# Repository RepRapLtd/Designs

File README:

This is just a dump of all my various designs for things that are not
specifically RepRap.

Some of the things here are OS designs that are not mine, and have just been placed
in this directory by me for convenience.

AB
24/2/2015

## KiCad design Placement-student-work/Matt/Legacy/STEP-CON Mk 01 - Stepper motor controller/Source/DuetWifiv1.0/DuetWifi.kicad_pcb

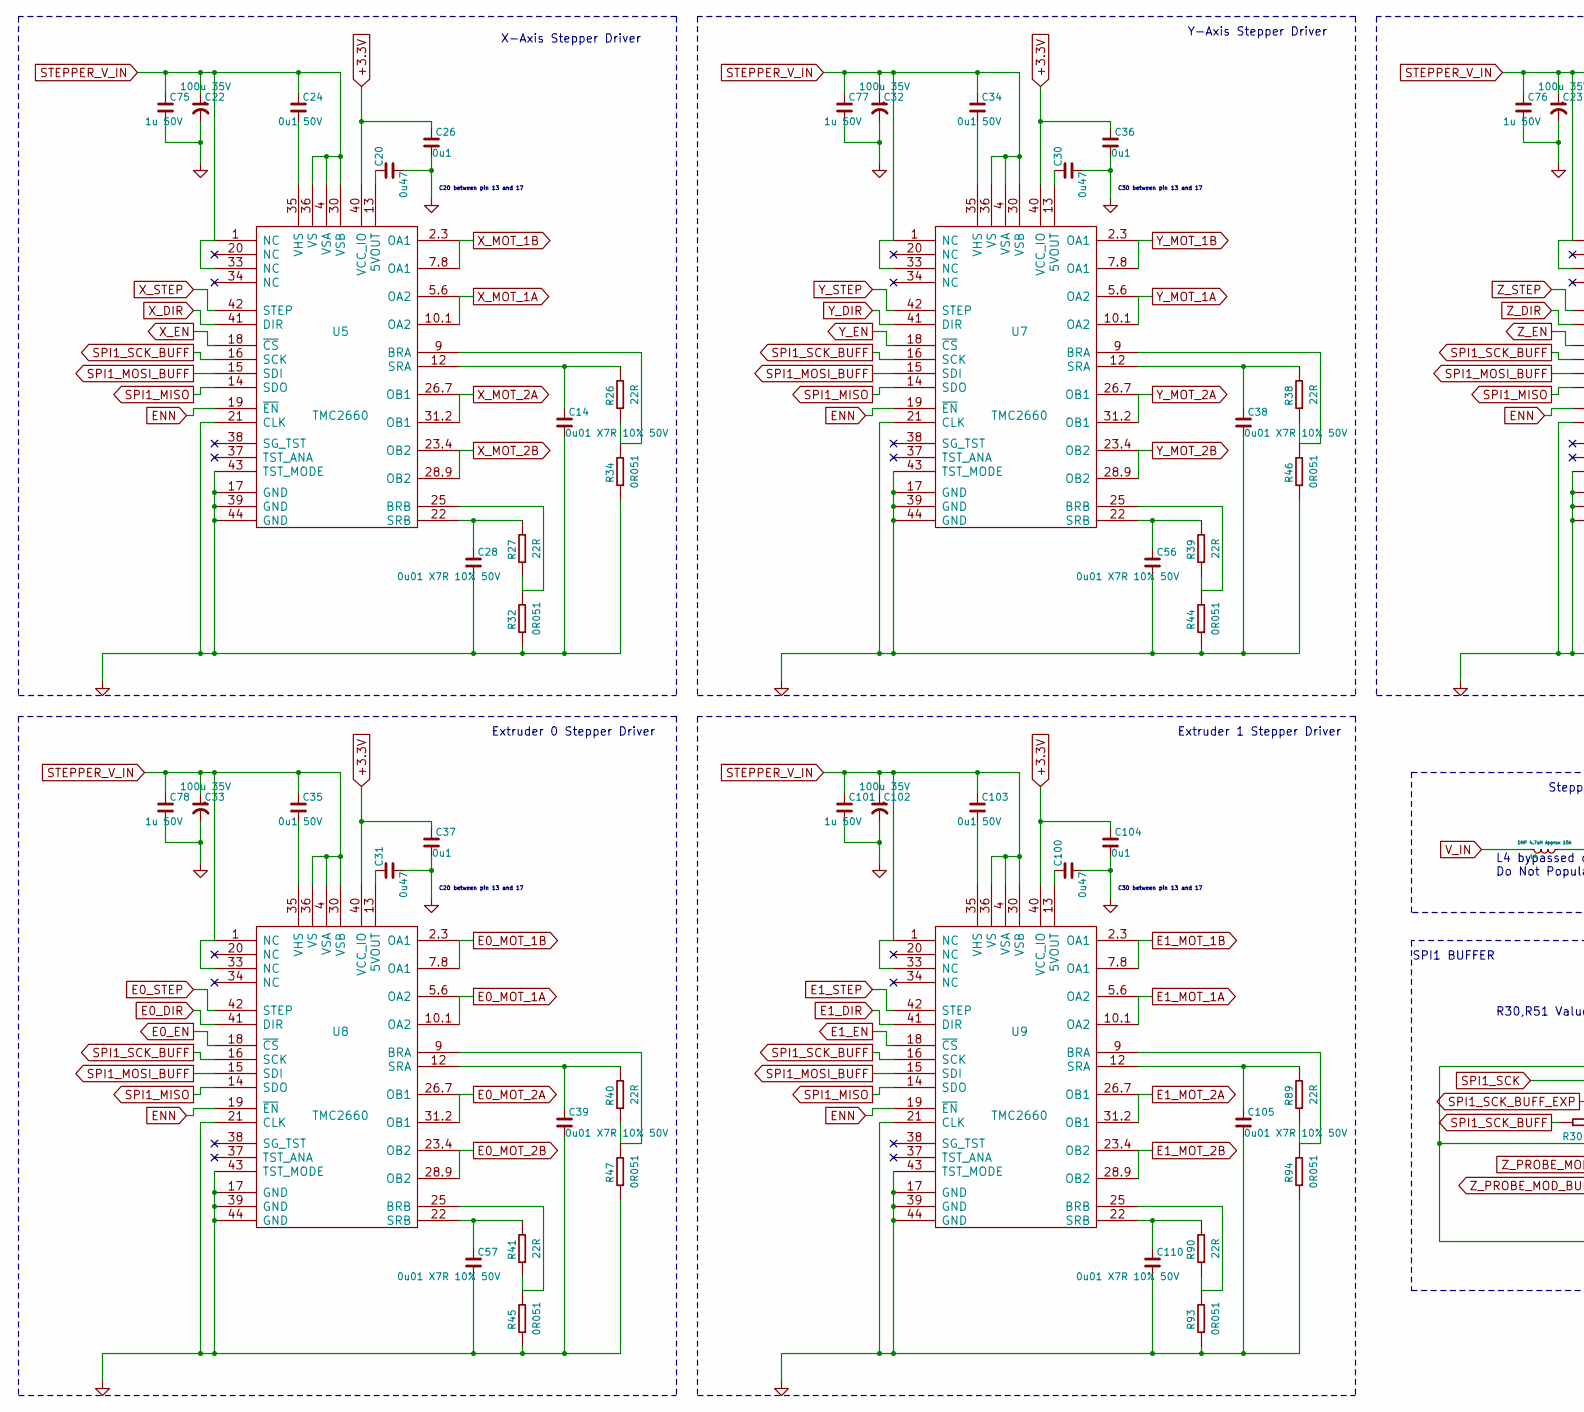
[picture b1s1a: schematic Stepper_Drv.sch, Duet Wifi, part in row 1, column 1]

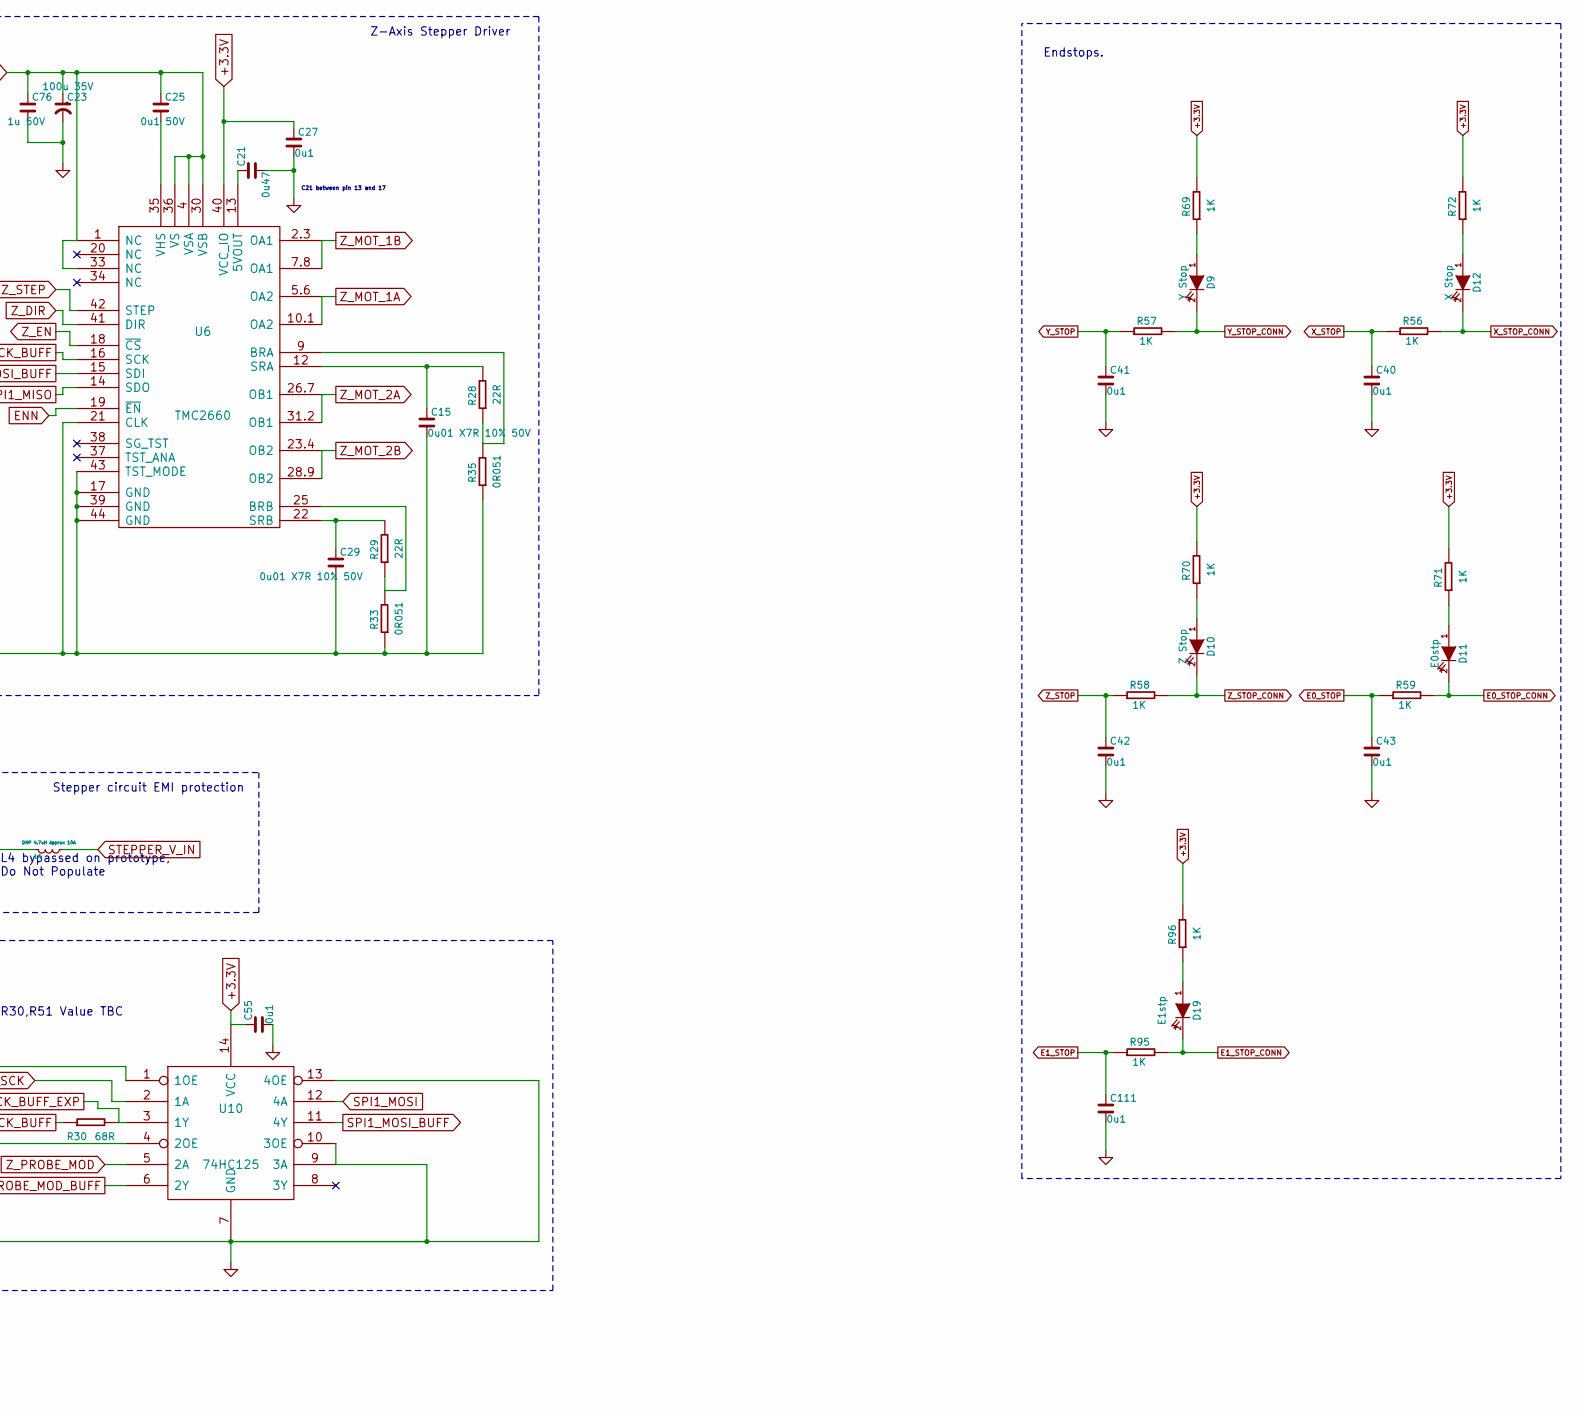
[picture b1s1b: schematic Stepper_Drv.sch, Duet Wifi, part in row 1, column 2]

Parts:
C14, C15, C28, C29, C38, C39, C56, C57, C105, C110: 0u01 X7R 10% 50V; C_0603
C20, C21, C30, C31, C100: 0u47; C_0603
C22, C23, C32, C33, C102: 100u 35V; C_ELEC_6.3x7.7
C24, C25, C34, C35, C103: 0u1 50V; C_0603
C26, C27, C36, C37, C40, C41, C42, C43, C55, C104, C111: 0u1; C_0603
C75, C76, C77, C78, C101: 1u 50V; C_0603
D9: Y Stop; D_0603
D10: Z Stop; D_0603
D11: E0stp; D_0603
D12: X Stop; D_0603
D19: E1stp; D_0603
L4: DNP 4.7uH Approx 10A; TPC-XL-Bridged
R26, R27, R28, R29, R38, R39, R40, R41, R89, R90: 22R; R_0603
R30: 68R; R_0603
R32, R33, R34, R35, R44, R45, R46, R47, R93, R94: 0R051; R_1206
R56, R57, R58, R59, R69, R70, R71, R72, R95, R96: 1K; R_0603
U5, U6, U7, U8, U9: TMC2660
U10: 74HC125; TSSOP-14

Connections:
+3.3V: C26.1, C27.1, C36.1, C37.1, C55.1, C104.1, R69.2, R70.2, R71.2, R72.2, R96.2, U5.40 (VCC_IO), U6.40 (VCC_IO), U7.40 (VCC_IO), U8.40 (VCC_IO), U9.40 (VCC_IO), U10.14 (VCC); also elsewhere on the board
E0_DIR: U8.41 (DIR); also elsewhere on the board
E0_EN: U8.18 (~CS); also elsewhere on the board
E0_MOT_1A: U8.5.6 (OA2), U8.10.1 (OA2); also elsewhere on the board
E0_MOT_1B: U8.2.3 (OA1), U8.7.8 (OA1); also elsewhere on the board
E0_MOT_2A: U8.26.7 (OB1), U8.31.2 (OB1); also elsewhere on the board
E0_MOT_2B: U8.23.4 (OB2), U8.28.9 (OB2); also elsewhere on the board
E0_STEP: U8.42 (STEP); also elsewhere on the board
E0_STOP: C43.1, R59.1; also elsewhere on the board
E0_STOP_CONN: D11.2 (K), R59.2; also elsewhere on the board
E1_DIR: U9.41 (DIR); also elsewhere on the board
E1_EN: U9.18 (~CS); also elsewhere on the board
E1_MOT_1A: U9.5.6 (OA2), U9.10.1 (OA2); also elsewhere on the board
E1_MOT_1B: U9.2.3 (OA1), U9.7.8 (OA1); also elsewhere on the board
E1_MOT_2A: U9.26.7 (OB1), U9.31.2 (OB1); also elsewhere on the board
E1_MOT_2B: U9.23.4 (OB2), U9.28.9 (OB2); also elsewhere on the board
E1_STEP: U9.42 (STEP); also elsewhere on the board
E1_STOP: C111.1, R95.1; also elsewhere on the board
E1_STOP_CONN: D19.2 (K), R95.2; also elsewhere on the board
ENN: U5.19 (~EN), U6.19 (~EN), U7.19 (~EN), U8.19 (~EN), U9.19 (~EN); also elsewhere on the board
GND: C14.2, C15.2, C20.2, C21.2, C22.2, C23.2, C26.2, C27.2, C28.2, C29.2, C30.2, C31.2, C32.2, C33.2, C36.2, C37.2, C38.2, C39.2, C40.2, C41.2, C42.2, C43.2, C55.2, C56.2, C57.2, C75.2, C76.2, C77.2, C78.2, C100.2, C101.2, C102.2, C104.2, C105.2, C110.2, C111.2, R32.1, R33.1, R34.1, R35.1, R44.1, R45.1, R46.1, R47.1, R93.1, R94.1, U5.17 (GND), U5.21 (CLK), U5.39 (GND), U5.43 (TST_MODE), U5.44 (GND), U6.17 (GND), U6.21 (CLK), U6.39 (GND), U6.43 (TST_MODE), U6.44 (GND), U7.17 (GND), U7.21 (CLK), U7.39 (GND), U7.43 (TST_MODE), U7.44 (GND), U8.17 (GND), U8.21 (CLK), U8.39 (GND), U8.43 (TST_MODE), U8.44 (GND), U9.17 (GND), U9.21 (CLK), U9.39 (GND), U9.43 (TST_MODE), U9.44 (GND), U10.1 (1OE), U10.4 (2OE), U10.7 (GND), U10.9 (3A), U10.10 (3OE), U10.13 (4OE); also elsewhere on the board
unnamed: C14.1, R26.2, U5.12 (SRA)
unnamed: C15.1, R28.2, U6.12 (SRA)
unnamed: C20.1, U5.13 (5VOUT)
unnamed: C21.1, U6.13 (5VOUT)
unnamed: C24.2, U5.35 (VHS)
unnamed: C25.2, U6.35 (VHS)
unnamed: C28.1, R27.2, U5.22 (SRB)
unnamed: C29.1, R29.2, U6.22 (SRB)
unnamed: C30.1, U7.13 (5VOUT)
unnamed: C31.1, U8.13 (5VOUT)
unnamed: C34.2, U7.35 (VHS)
unnamed: C35.2, U8.35 (VHS)
unnamed: C38.1, R38.2, U7.12 (SRA)
unnamed: C39.1, R40.2, U8.12 (SRA)
unnamed: C56.1, R39.2, U7.22 (SRB)
unnamed: C57.1, R41.2, U8.22 (SRB)
unnamed: C100.1, U9.13 (5VOUT)
unnamed: C103.2, U9.35 (VHS)
unnamed: C105.1, R89.2, U9.12 (SRA)
unnamed: C110.1, R90.2, U9.22 (SRB)
unnamed: D9.1 (A), R69.1
unnamed: D10.1 (A), R70.1
unnamed: D11.1 (A), R71.1
unnamed: D12.1 (A), R72.1
unnamed: D19.1 (A), R96.1
unnamed: R26.1, R34.2, U5.9 (BRA)
unnamed: R27.1, R32.2, U5.25 (BRB)
unnamed: R28.1, R35.2, U6.9 (BRA)
unnamed: R29.1, R33.2, U6.25 (BRB)
unnamed: R38.1, R46.2, U7.9 (BRA)
unnamed: R39.1, R44.2, U7.25 (BRB)
unnamed: R40.1, R47.2, U8.9 (BRA)
unnamed: R41.1, R45.2, U8.25 (BRB)
unnamed: R89.1, R94.2, U9.9 (BRA)
unnamed: R90.1, R93.2, U9.25 (BRB)
SPI1_MISO: U5.14 (SDO), U6.14 (SDO), U7.14 (SDO), U8.14 (SDO), U9.14 (SDO); also elsewhere on the board
SPI1_MOSI: U10.12 (4A); also elsewhere on the board
SPI1_MOSI_BUFF: U5.15 (SDI), U6.15 (SDI), U7.15 (SDI), U8.15 (SDI), U9.15 (SDI), U10.11 (4Y); also elsewhere on the board
SPI1_SCK: U10.2 (1A); also elsewhere on the board
SPI1_SCK_BUFF: R30.1, U5.16 (SCK), U6.16 (SCK), U7.16 (SCK), U8.16 (SCK), U9.16 (SCK); also elsewhere on the board
SPI1_SCK_BUFF_EXP: R30.2, U10.3 (1Y); also elsewhere on the board
STEPPER_V_IN: C22.1, C23.1, C24.1, C25.1, C32.1, C33.1, C34.1, C35.1, C75.1, C76.1, C77.1, C78.1, C101.1, C102.1, C103.1, L4.2 (B), U5.1 (NC), U5.4 (VSA), U5.30 (VSB), U5.33 (NC), U5.36 (VS), U6.1 (NC), U6.4 (VSA), U6.30 (VSB), U6.33 (NC), U6.36 (VS), U7.1 (NC), U7.4 (VSA), U7.30 (VSB), U7.33 (NC), U7.36 (VS), U8.1 (NC), U8.4 (VSA), U8.30 (VSB), U8.33 (NC), U8.36 (VS), U9.1 (NC), U9.4 (VSA), U9.30 (VSB), U9.33 (NC), U9.36 (VS)
V_IN: L4.1 (A); also elsewhere on the board
X_DIR: U5.41 (DIR); also elsewhere on the board
X_EN: U5.18 (~CS); also elsewhere on the board
X_MOT_1A: U5.5.6 (OA2), U5.10.1 (OA2); also elsewhere on the board
X_MOT_1B: U5.2.3 (OA1), U5.7.8 (OA1); also elsewhere on the board
X_MOT_2A: U5.26.7 (OB1), U5.31.2 (OB1); also elsewhere on the board
X_MOT_2B: U5.23.4 (OB2), U5.28.9 (OB2); also elsewhere on the board
X_STEP: U5.42 (STEP); also elsewhere on the board
X_STOP: C40.1, R56.1; also elsewhere on the board
X_STOP_CONN: D12.2 (K), R56.2; also elsewhere on the board
Y_DIR: U7.41 (DIR); also elsewhere on the board
Y_EN: U7.18 (~CS); also elsewhere on the board
Y_MOT_1A: U7.5.6 (OA2), U7.10.1 (OA2); also elsewhere on the board
Y_MOT_1B: U7.2.3 (OA1), U7.7.8 (OA1); also elsewhere on the board
Y_MOT_2A: U7.26.7 (OB1), U7.31.2 (OB1); also elsewhere on the board
Y_MOT_2B: U7.23.4 (OB2), U7.28.9 (OB2); also elsewhere on the board
Y_STEP: U7.42 (STEP); also elsewhere on the board
Y_STOP: C41.1, R57.1; also elsewhere on the board
Y_STOP_CONN: D9.2 (K), R57.2; also elsewhere on the board
Z_DIR: U6.41 (DIR); also elsewhere on the board
Z_EN: U6.18 (~CS); also elsewhere on the board
Z_MOT_1A: U6.5.6 (OA2), U6.10.1 (OA2); also elsewhere on the board
Z_MOT_1B: U6.2.3 (OA1), U6.7.8 (OA1); also elsewhere on the board
Z_MOT_2A: U6.26.7 (OB1), U6.31.2 (OB1); also elsewhere on the board
Z_MOT_2B: U6.23.4 (OB2), U6.28.9 (OB2); also elsewhere on the board
Z_PROBE_MOD: U10.5 (2A); also elsewhere on the board
Z_PROBE_MOD_BUFF: U10.6 (2Y); also elsewhere on the board
Z_STEP: U6.42 (STEP); also elsewhere on the board
Z_STOP: C42.1, R58.1; also elsewhere on the board
Z_STOP_CONN: D10.2 (K), R58.2; also elsewhere on the board

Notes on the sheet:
Endstops.
Extruder 0 Stepper Driver
Y-Axis Stepper Driver
X-Axis Stepper Driver
Extruder 1 Stepper Driver
Stepper circuit EMI protection
L4 bypassed on prototype, Do Not Populate
SPI1 BUFFER
C20 between pin 13 and 17
C30 between pin 13 and 17
Z-Axis Stepper Driver
C21 between pin 13 and 17
R30,R51 Value TBC

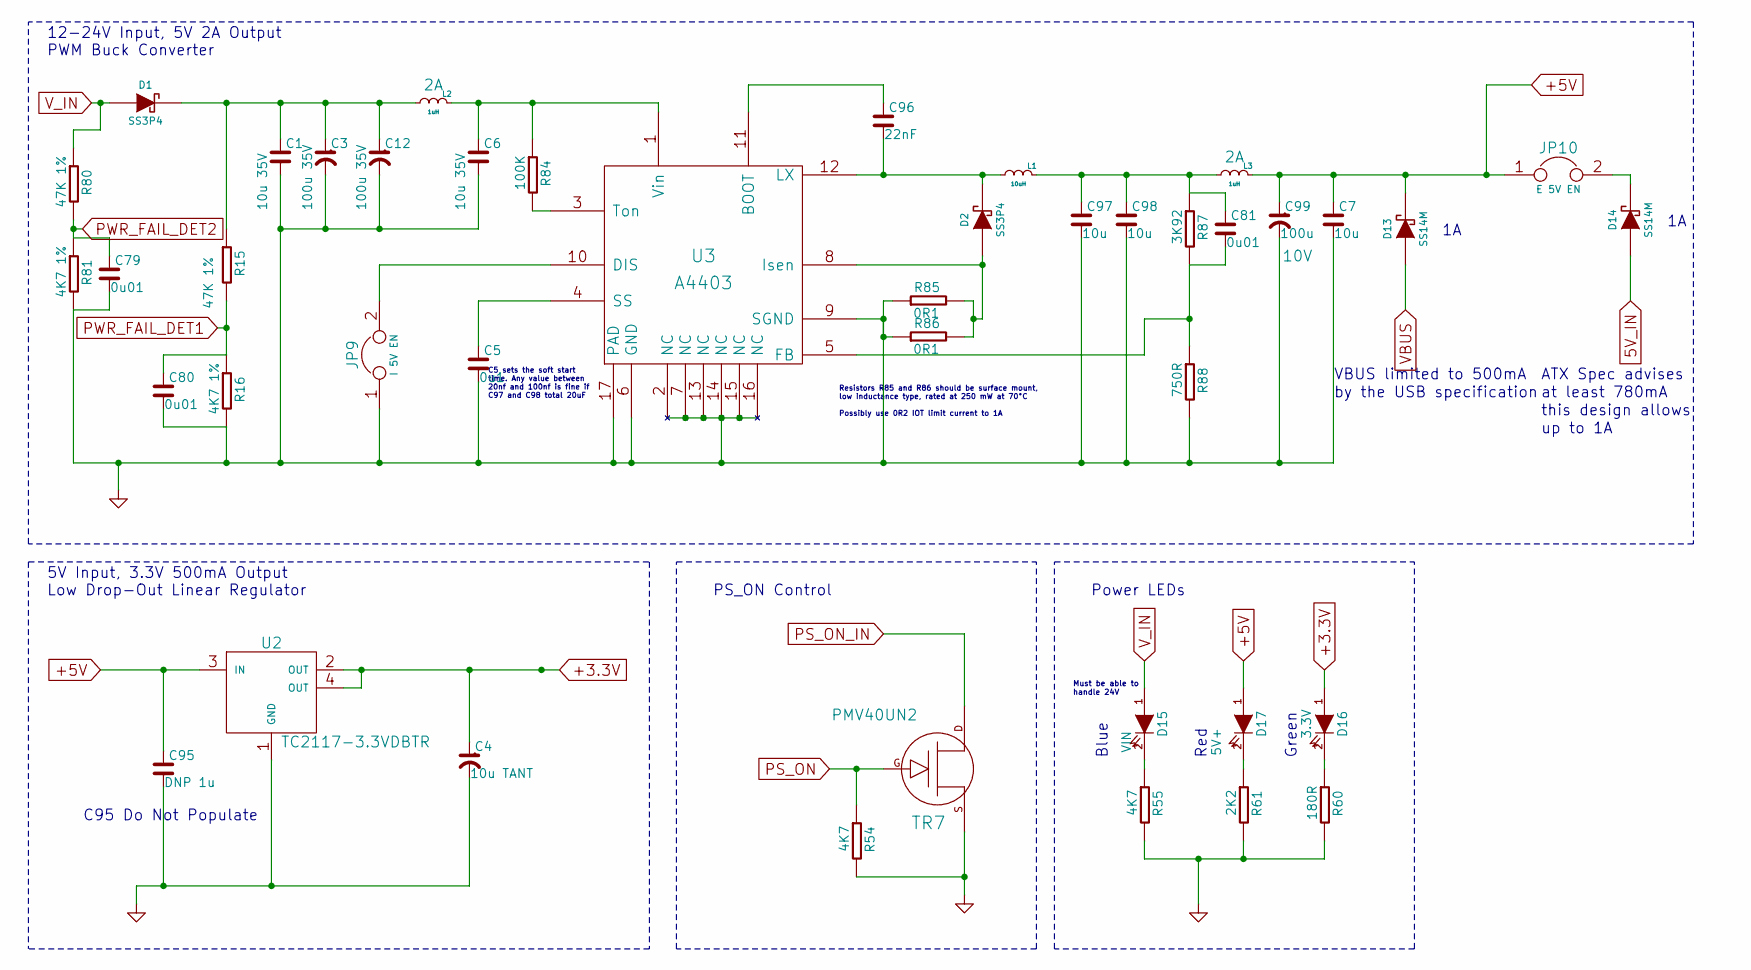
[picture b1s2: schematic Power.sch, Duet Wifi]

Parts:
C1, C6: 10u 35V; C_1206
C3, C12: 100u 35V; C_ELEC_6.3x7.7
C4: 10u TANT; C_1206_pol
C5: 0u1; C_0603
C7, C97, C98: 10u; C_0805
C79, C80, C81: 0u01; C_0603
C95: DNP 1u; C_0603
C96: 22nF; C_0603
C99: 100u; C_ELEC_6.3x7.7; Voltage 10V
D1, D2: SS3P4; DO-220AA
D13, D14: SS14M; uSMA
D15: VIN; D_0603
D16: 3.3V; D_0603
D17: 5V+; D_0603
JP9: I 5V EN; JUMPER
JP10: E 5V EN; JUMPER
L1: 10uH; L_6x6
L2, L3: 1uH; C_1210; Rating 2A
R15, R80: 47K 1%; R_0603
R16, R81: 4K7 1%; R_0603
R54, R55: 4K7; R_0603
R60: 180R; R_0603
R61: 2K2; R_0603
R84: 100K; R_0603
R85, R86: 0R1; R_1206
R87: 3K92; R_0603
R88: 750R; R_0603
TR7: PMV40UN2; SOT-23
U2: TC2117-3.3VDBTR; SOT-223
U3: A4403; QFN16-4x4

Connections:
5V_IN: D14.1 (A); also elsewhere on the board
+3.3V: C4.1, D16.1 (A), U2.2 (OUT), U2.4 (OUT); also elsewhere on the board
+5V: C7.1, C95.1, C99.1, D13.2 (K), D17.1 (A), JP10.1, L3.1 (A), U2.3 (IN); also elsewhere on the board
GND: C1.2, C3.2, C4.2, C5.2, C6.2, C7.2, C12.2, C79.2, C80.2, C95.2, C97.2, C98.2, C99.2, JP9.1, R16.2, R54.2, R55.2, R60.2, R61.2, R81.2, R85.1, R86.1, R88.2, TR7.S, U2.1 (GND), U3.2 (NC), U3.6 (GND), U3.7 (NC), U3.9 (SGND), U3.13 (NC), U3.14 (NC), U3.15 (NC), U3.16 (NC), U3.17 (PAD); also elsewhere on the board
unnamed: C1.1, C3.1, C12.1, D1.2 (K), L2.2 (B), R15.1
unnamed: C5.1, U3.4 (SS)
unnamed: C6.1, L2.1 (A), R84.1, U3.1 (Vin)
unnamed: C81.1, C97.1, C98.1, L1.1 (A), L3.2 (B), R87.1
unnamed: C81.2, R87.2, R88.1, U3.5 (FB)
unnamed: C96.1, U3.11 (BOOT)
unnamed: C96.2, D2.2 (K), L1.2 (B), U3.12 (LX)
unnamed: D2.1 (A), R85.2, R86.2, U3.8 (Isen)
unnamed: D14.2 (K), JP10.2
unnamed: D15.2 (K), R55.1
unnamed: D16.2 (K), R60.1
unnamed: D17.2 (K), R61.1
unnamed: JP9.2, U3.10 (DIS)
unnamed: R84.2, U3.3 (Ton)
PS_ON: R54.1, TR7.G; also elsewhere on the board
PS_ON_IN: TR7.D; also elsewhere on the board
PWR_FAIL_DET1: C80.1, R15.2, R16.1; also elsewhere on the board
PWR_FAIL_DET2: C79.1, R80.2, R81.1; also elsewhere on the board
VBUS: D13.1 (A); also elsewhere on the board
V_IN: D1.1 (A), D15.1 (A), R80.1; also elsewhere on the board

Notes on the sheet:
PS_ON Control
up to 1A
this design allows
at least 780mA
ATX Spec advises
by the USB specification
VBUS limited to 500mA
5V Input, 3.3V 500mA Output Low Drop-Out Linear Regulator
12-24V Input, 5V 2A Output PWM Buck Converter
Resistors R85 and R86 should be surface mount, low inductance type, rated at 250 mW at 70°C Possibly use 0R2 IOT limit current to 1A
C5 sets the soft start time. Any value between 20nf and 100nf is fine if C97 and C98 total 20uF
Power LEDs
Must be able to handle 24V
Blue
Red
Green
C95 Do Not Populate

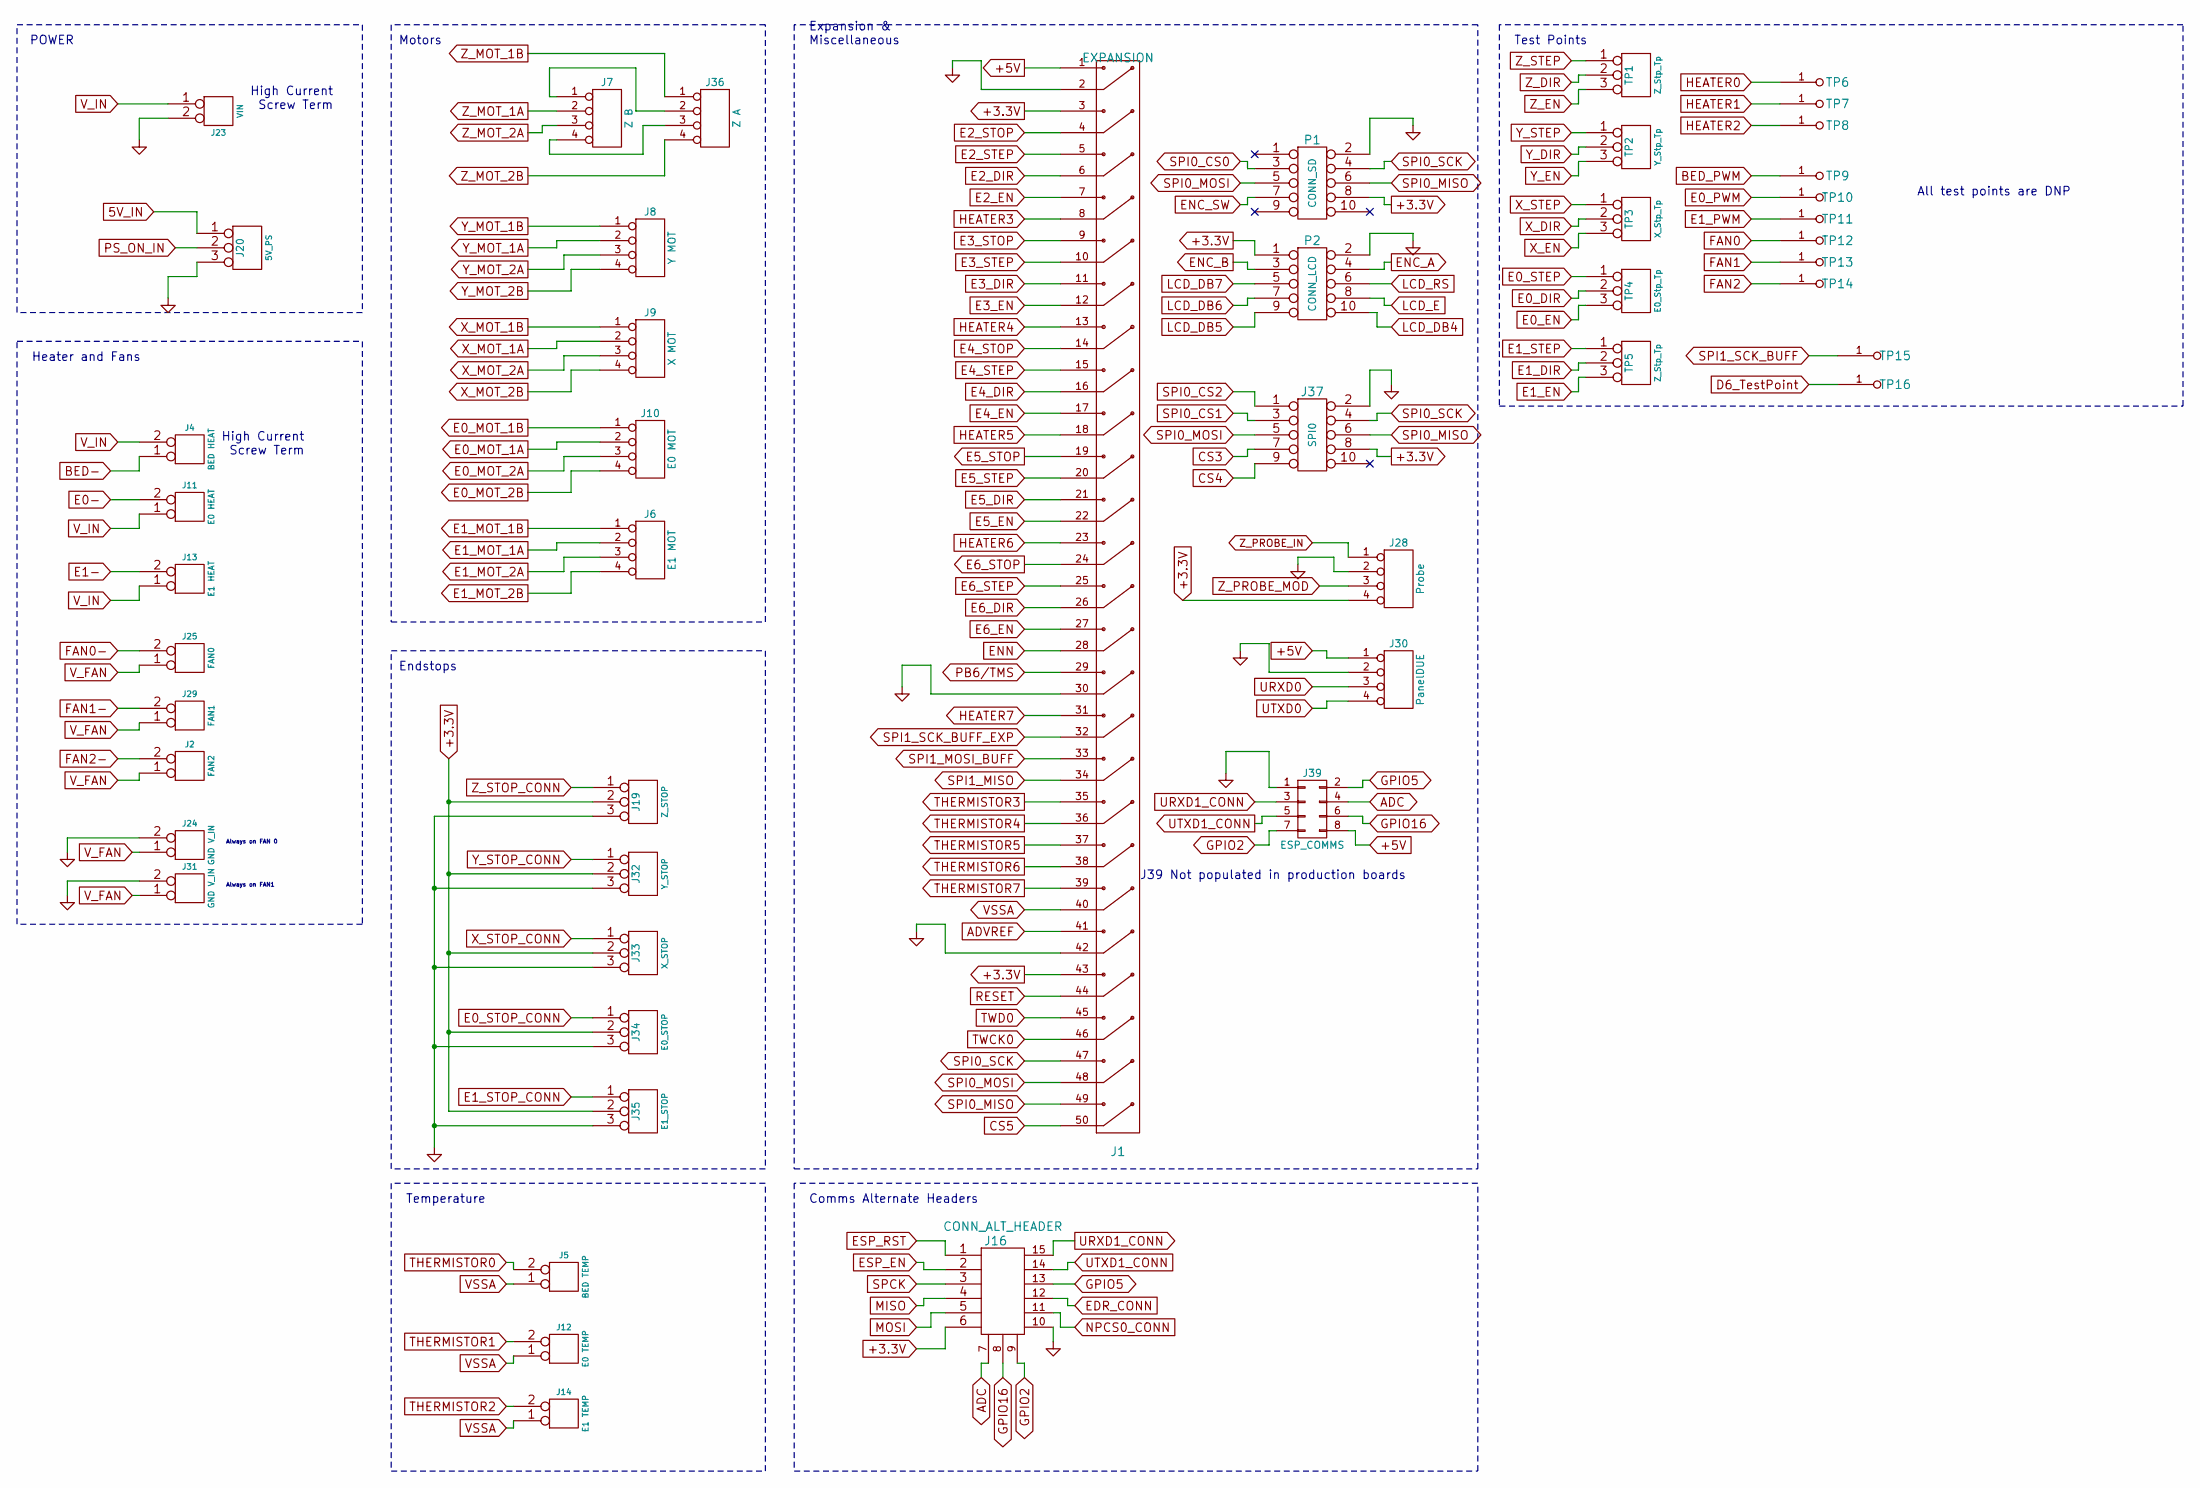
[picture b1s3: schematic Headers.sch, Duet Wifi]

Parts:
J1: EXPANSION; PIN_ARRAY_25X2
J2: FAN2; PIN_ARRAY_2X1
J4: BED HEAT; TERM_2-WAY_6.35mm
J5: BED TEMP; PIN_ARRAY_2X1
J6: E1 MOT; PIN_ARRAY_4x1
J7: Z B; PIN_ARRAY_4x1
J8: Y MOT; PIN_ARRAY_4x1
J9: X MOT; PIN_ARRAY_4x1
J10: E0 MOT; PIN_ARRAY_4x1
J11: E0 HEAT; 3.5MM_2X1
J12: E0 TEMP; PIN_ARRAY_2X1
J13: E1 HEAT; 3.5MM_2X1
J14: E1 TEMP; PIN_ARRAY_2X1
J16: CONN_ALT_HEADER
J19: Z_STOP; PIN_ARRAY_3X1
J20: 5V_PS; PIN_ARRAY_3X1
J23: VIN; TERM_2-WAY_6.35mm
J24, J31: GND V_IN; PIN_ARRAY_2X1
J25: FAN0; PIN_ARRAY_2X1
J28: Probe; PIN_ARRAY_4x1
J29: FAN1; PIN_ARRAY_2X1
J30: PanelDUE; PIN_ARRAY_4x1
J32: Y_STOP; PIN_ARRAY_3X1
J33: X_STOP; PIN_ARRAY_3X1
J34: E0_STOP; PIN_ARRAY_3X1
J35: E1_STOP; PIN_ARRAY_3X1
J36: Z A; PIN_ARRAY_4x1
J37: SPI0; MAX_TEMP_DB
J39: ESP_COMMS; CONN_4x2
P1: CONN_SD; IDC_PIN_ARRAY_5x2
P2: CONN_LCD; IDC_PIN_ARRAY_5x2
TP1, TP5: Z_Stp_Tp; CONN_3x1
TP2: Y_Stp_Tp; CONN_3x1
TP3: X_Stp_Tp; CONN_3x1
TP4: E0_Stp_Tp; CONN_3x1
TP6, TP7, TP8, TP9, TP10, TP11, TP12, TP13, TP14, TP15, TP16: TP; TP_via

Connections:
5V_IN: J20.1; also elsewhere on the board
+3.3V: J1.3, J1.43, J16.6, J19.2 (PM), J28.4, J32.2 (PM), J33.2 (PM), J34.2 (PM), J35.2 (PM), J37.8, P1.8, P2.1; also elsewhere on the board
+5V: J1.1, J30.1, J39.8; also elsewhere on the board
ADC: J16.7, J39.4; also elsewhere on the board
ADVREF: J1.41; also elsewhere on the board
BED-: J4.1; also elsewhere on the board
BED_PWM: TP9.1; also elsewhere on the board
CS3: J37.7; also elsewhere on the board
CS4: J37.9; also elsewhere on the board
CS5: J1.50; also elsewhere on the board
D6_TestPoint: TP16.1; also elsewhere on the board
E0-: J11.2 (PM); also elsewhere on the board
E0_DIR: TP4.2 (PM); also elsewhere on the board
E0_EN: TP4.3; also elsewhere on the board
E0_MOT_1A: J10.2; also elsewhere on the board
E0_MOT_1B: J10.1; also elsewhere on the board
E0_MOT_2A: J10.3; also elsewhere on the board
E0_MOT_2B: J10.4; also elsewhere on the board
E0_PWM: TP10.1; also elsewhere on the board
E0_STEP: TP4.1; also elsewhere on the board
E0_STOP_CONN: J34.1; also elsewhere on the board
E1-: J13.2 (PM); also elsewhere on the board
E1_DIR: TP5.2 (PM); also elsewhere on the board
E1_EN: TP5.3; also elsewhere on the board
E1_MOT_1A: J6.2; also elsewhere on the board
E1_MOT_1B: J6.1; also elsewhere on the board
E1_MOT_2A: J6.3; also elsewhere on the board
E1_MOT_2B: J6.4; also elsewhere on the board
E1_PWM: TP11.1; also elsewhere on the board
E1_STEP: TP5.1; also elsewhere on the board
E1_STOP_CONN: J35.1; also elsewhere on the board
E2_DIR: J1.6; also elsewhere on the board
E2_EN: J1.7; also elsewhere on the board
E2_STEP: J1.5; also elsewhere on the board
E2_STOP: J1.4; also elsewhere on the board
E3_DIR: J1.11; also elsewhere on the board
E3_EN: J1.12; also elsewhere on the board
E3_STEP: J1.10; also elsewhere on the board
E3_STOP: J1.9; also elsewhere on the board
E4_DIR: J1.16; also elsewhere on the board
E4_EN: J1.17; also elsewhere on the board
E4_STEP: J1.15; also elsewhere on the board
E4_STOP: J1.14; also elsewhere on the board
E5_DIR: J1.21; also elsewhere on the board
E5_EN: J1.22; also elsewhere on the board
E5_STEP: J1.20; also elsewhere on the board
E5_STOP: J1.19; also elsewhere on the board
E6_DIR: J1.26; also elsewhere on the board
E6_EN: J1.27; also elsewhere on the board
E6_STEP: J1.25; also elsewhere on the board
E6_STOP: J1.24; also elsewhere on the board
EDR_CONN: J16.12; also elsewhere on the board
ENC_A: P2.4; also elsewhere on the board
ENC_B: P2.3; also elsewhere on the board
ENC_SW: P1.7; also elsewhere on the board
ENN: J1.28; also elsewhere on the board
ESP_EN: J16.2; also elsewhere on the board
ESP_RST: J16.1; also elsewhere on the board
FAN0: TP12.1; also elsewhere on the board
FAN0-: J25.2 (PM); also elsewhere on the board
FAN1: TP13.1; also elsewhere on the board
FAN1-: J29.2 (PM); also elsewhere on the board
FAN2: TP14.1; also elsewhere on the board
FAN2-: J2.2 (PM); also elsewhere on the board
GND: J1.2, J1.30, J1.42, J16.10, J19.3, J20.3, J23.2 (PM), J24.2 (PM), J28.2, J30.2, J31.2 (PM), J32.3, J33.3, J34.3, J35.3, J37.2, J39.1, P1.2, P2.2; also elsewhere on the board
GPIO2: J16.9, J39.7; also elsewhere on the board
GPIO5: J16.13, J39.2; also elsewhere on the board
GPIO16: J16.8, J39.6; also elsewhere on the board
HEATER0: TP6.1; also elsewhere on the board
HEATER1: TP7.1; also elsewhere on the board
HEATER2: TP8.1; also elsewhere on the board
HEATER3: J1.8; also elsewhere on the board
HEATER4: J1.13; also elsewhere on the board
HEATER5: J1.18; also elsewhere on the board
HEATER6: J1.23; also elsewhere on the board
HEATER7: J1.31; also elsewhere on the board
LCD_DB4: P2.10; also elsewhere on the board
LCD_DB5: P2.9; also elsewhere on the board
LCD_DB6: P2.7; also elsewhere on the board
LCD_DB7: P2.5; also elsewhere on the board
LCD_E: P2.8; also elsewhere on the board
LCD_RS: P2.6; also elsewhere on the board
MISO: J16.4; also elsewhere on the board
MOSI: J16.5; also elsewhere on the board
NPCS0_CONN: J16.11; also elsewhere on the board
unnamed: J7.1, J36.2
unnamed: J7.4, J36.3
PB6/TMS: J1.29; also elsewhere on the board
PS_ON_IN: J20.2 (PM); also elsewhere on the board
RESET: J1.44; also elsewhere on the board
SPCK: J16.3; also elsewhere on the board
SPI0_CS0: P1.3; also elsewhere on the board
SPI0_CS1: J37.3; also elsewhere on the board
SPI0_CS2: J37.1; also elsewhere on the board
SPI0_MISO: J1.49, J37.6, P1.6; also elsewhere on the board
SPI0_MOSI: J1.48, J37.5, P1.5; also elsewhere on the board
SPI0_SCK: J1.47, J37.4, P1.4; also elsewhere on the board
SPI1_MISO: J1.34; also elsewhere on the board
SPI1_MOSI_BUFF: J1.33; also elsewhere on the board
SPI1_SCK_BUFF: TP15.1; also elsewhere on the board
SPI1_SCK_BUFF_EXP: J1.32; also elsewhere on the board
THERMISTOR0: J5.2 (PM); also elsewhere on the board
THERMISTOR1: J12.2 (PM); also elsewhere on the board
THERMISTOR2: J14.2 (PM); also elsewhere on the board
THERMISTOR3: J1.35; also elsewhere on the board
THERMISTOR4: J1.36; also elsewhere on the board
THERMISTOR5: J1.37; also elsewhere on the board
THERMISTOR6: J1.38; also elsewhere on the board
THERMISTOR7: J1.39; also elsewhere on the board
TWCK0: J1.46; also elsewhere on the board
TWD0: J1.45; also elsewhere on the board
URXD0: J30.3; also elsewhere on the board
URXD1_CONN: J16.15, J39.3; also elsewhere on the board
UTXD0: J30.4; also elsewhere on the board
UTXD1_CONN: J16.14, J39.5; also elsewhere on the board
VSSA: J1.40, J5.1, J12.1, J14.1; also elsewhere on the board
V_FAN: J2.1, J24.1, J25.1, J29.1, J31.1; also elsewhere on the board
V_IN: J4.2 (PM), J11.1, J13.1, J23.1; also elsewhere on the board
X_DIR: TP3.2 (PM); also elsewhere on the board
X_EN: TP3.3; also elsewhere on the board
X_MOT_1A: J9.2; also elsewhere on the board
X_MOT_1B: J9.1; also elsewhere on the board
X_MOT_2A: J9.3; also elsewhere on the board
X_MOT_2B: J9.4; also elsewhere on the board
X_STEP: TP3.1; also elsewhere on the board
X_STOP_CONN: J33.1; also elsewhere on the board
Y_DIR: TP2.2 (PM); also elsewhere on the board
Y_EN: TP2.3; also elsewhere on the board
Y_MOT_1A: J8.2; also elsewhere on the board
Y_MOT_1B: J8.1; also elsewhere on the board
Y_MOT_2A: J8.3; also elsewhere on the board
Y_MOT_2B: J8.4; also elsewhere on the board
Y_STEP: TP2.1; also elsewhere on the board
Y_STOP_CONN: J32.1; also elsewhere on the board
Z_DIR: TP1.2 (PM); also elsewhere on the board
Z_EN: TP1.3; also elsewhere on the board
Z_MOT_1A: J7.2; also elsewhere on the board
Z_MOT_1B: J36.1; also elsewhere on the board
Z_MOT_2A: J7.3; also elsewhere on the board
Z_MOT_2B: J36.4; also elsewhere on the board
Z_PROBE_IN: J28.1; also elsewhere on the board
Z_PROBE_MOD: J28.3; also elsewhere on the board
Z_STEP: TP1.1; also elsewhere on the board
Z_STOP_CONN: J19.1; also elsewhere on the board

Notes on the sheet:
High Current Screw Term
Always on FAN 0
Always on FAN1
POWER
Heater and Fans
Temperature
Motors
Endstops
Expansion & Miscellaneous
J39 Not populated in production boards
Comms Alternate Headers
Test Points
All test points are DNP
